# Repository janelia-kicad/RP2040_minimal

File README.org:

# This file is generated automatically from metadata
# File edits may be overwritten!
- Project Name: RP2040_minimal
- Synopsis: This minimal design example is intended to demonstrate how you can get started with your own RP2040 based PCB designs.
- Documentation Version: 1.0.0
- Pcb Version: 1.0
- Enclosure Version: 1.0
- Supplemental BOM Version: 1.0
- Release Date: 2024-04-24
- Creation Date: 2024-03-20
- Kicad Version: 7.0.11
- License: BSD-3-Clause
- URL: https://github.com/janelia-kicad/RP2040_minimal
- Author: Peter Polidoro
- Email: peter@polidoro.io
- Copyright: 2024 Howard Hughes Medical Institute
- References:
  - [[https://www.raspberrypi.com/products/raspberry-pi-pico/][Raspberry Pi Pico]]

[[./documentation/pcb/raytrace.png]]

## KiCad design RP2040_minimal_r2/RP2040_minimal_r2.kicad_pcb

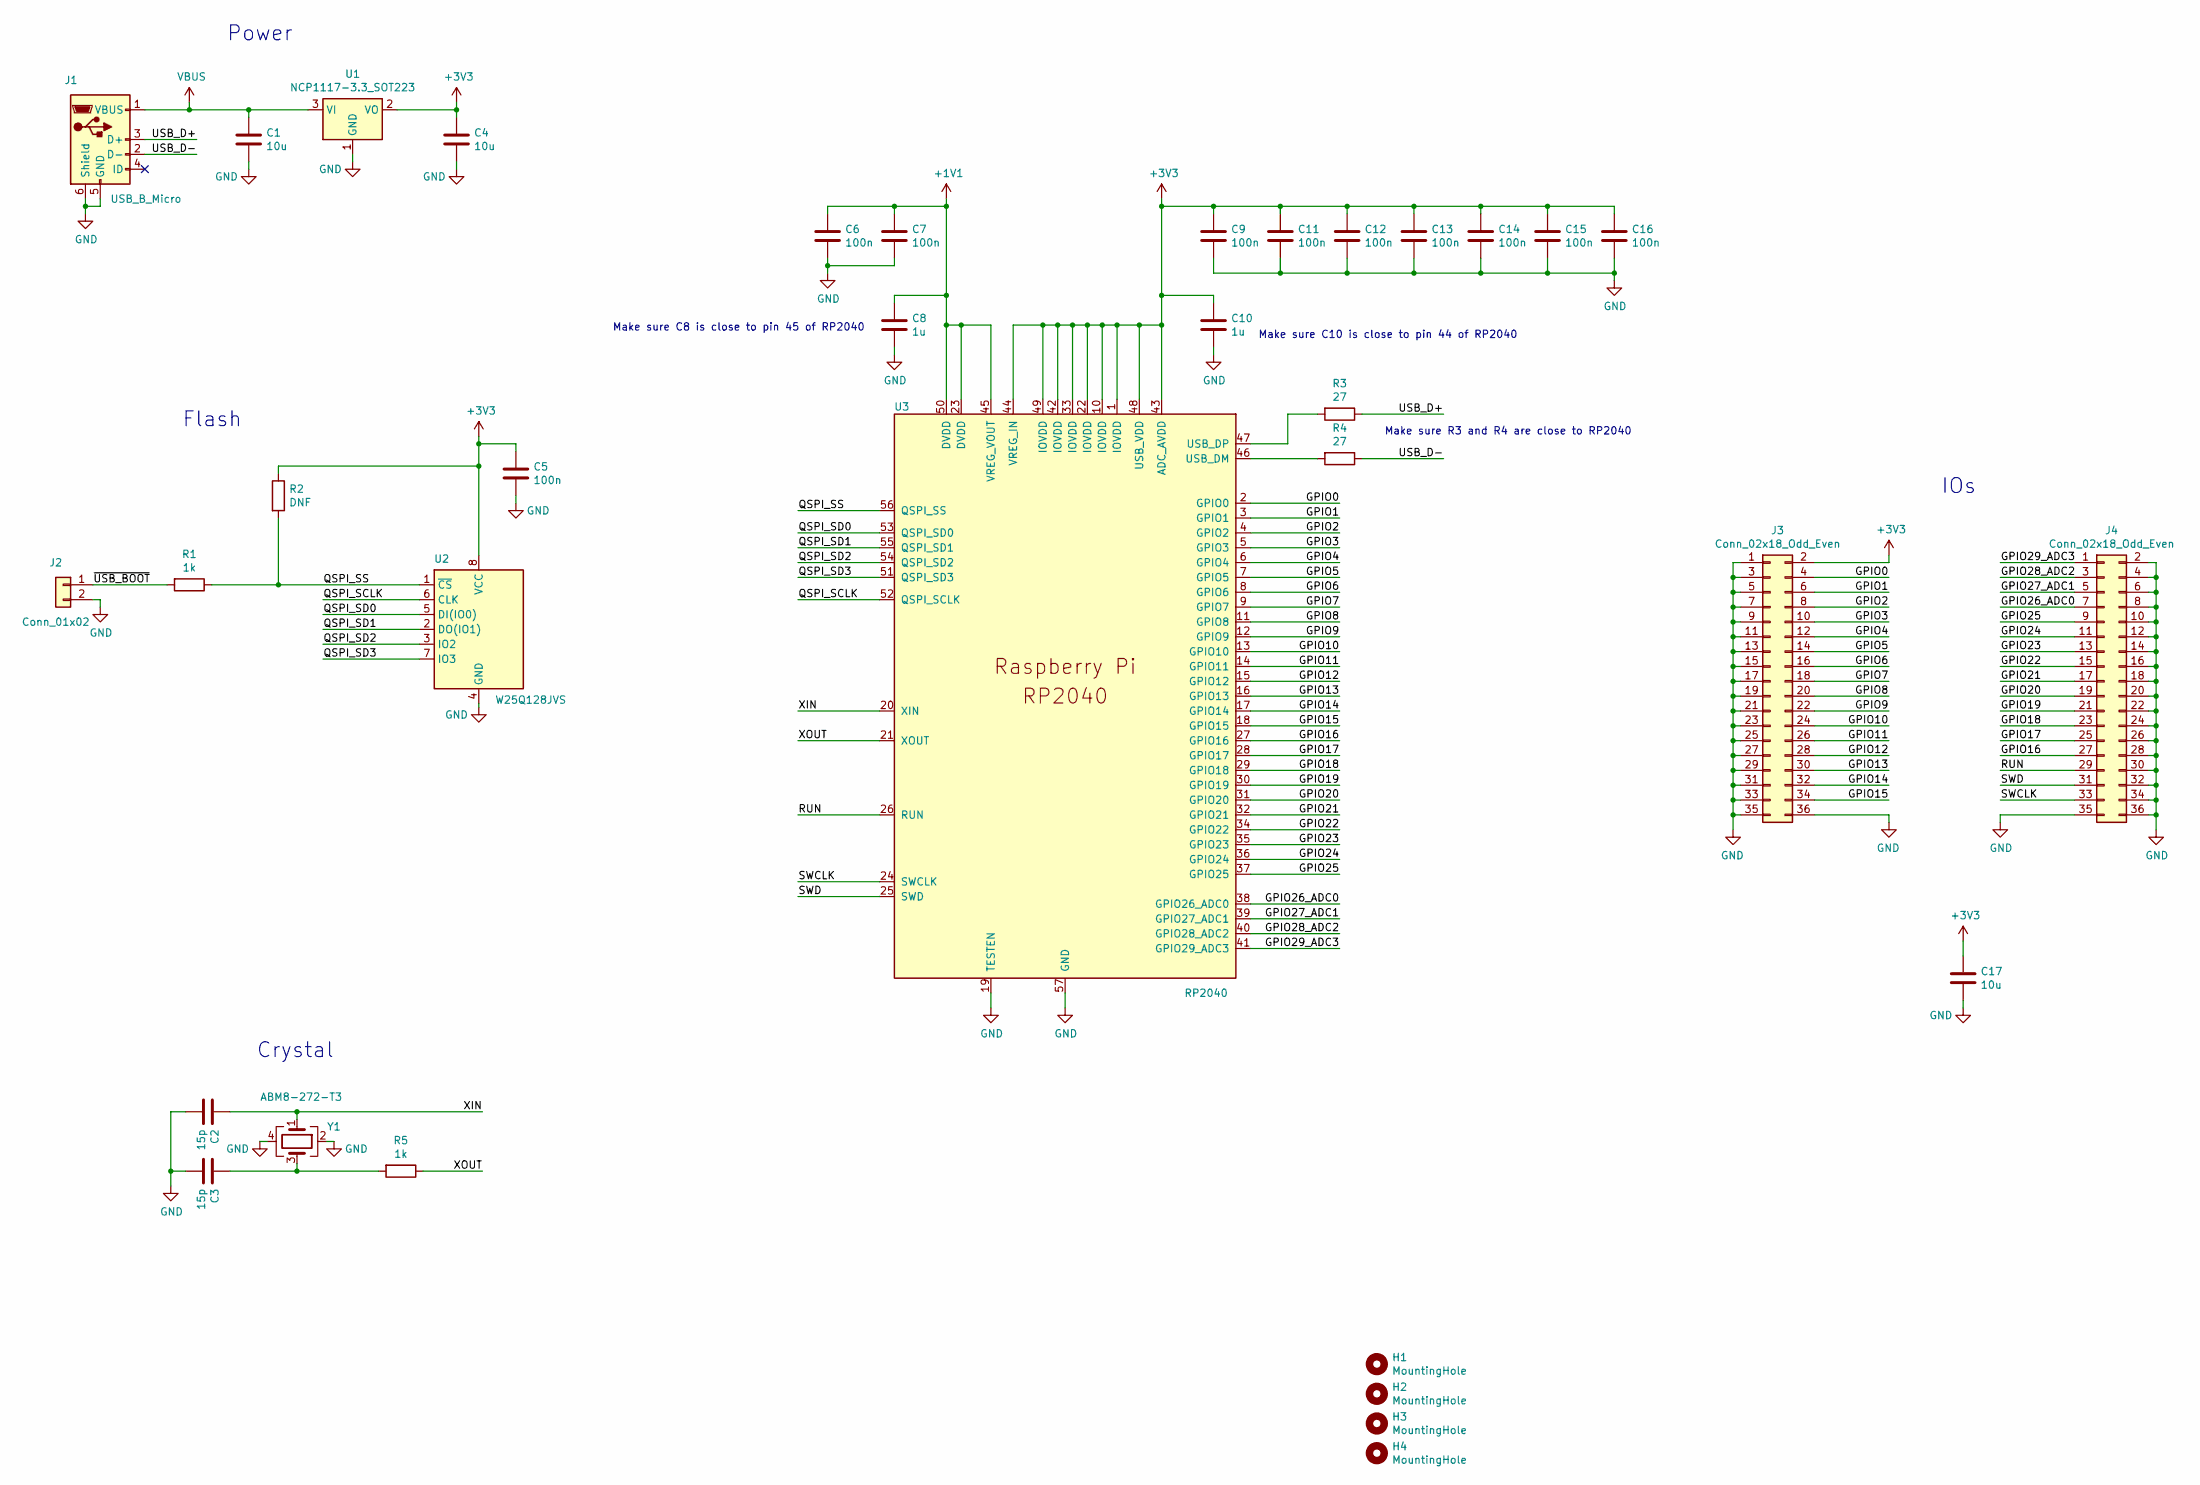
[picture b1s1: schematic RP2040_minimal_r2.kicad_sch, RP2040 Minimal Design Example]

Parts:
C1, C4, C17: 10u; C_0805_2012Metric
C2, C3: 15p; C_0402_1005Metric
C5, C6, C7, C9, C11, C12, C13, C14, C15, C16: 100n; C_0402_1005Metric
C8, C10: 1u; C_0402_1005Metric
H1, H2, H3, H4: MountingHole; MountingHole_2.7mm_M2.5
J1: USB_B_Micro; USB_Micro-B_Amphenol_10103594-0001LF_Horizontal_modified
J2: Conn_01x02; PinHeader_1x02_P2.54mm_Vertical
J3, J4: Conn_02x18_Odd_Even; PinHeader_2x18_P2.54mm_Vertical
R1, R5: 1k; R_0402_1005Metric
R2: DNF; R_0402_1005Metric
R3, R4: 27; R_0402_1005Metric
U1: NCP1117-3.3_SOT223; SOT-223-3_TabPin2
U2: W25Q128JVS; SOIC-8_5.23x5.23mm_P1.27mm
U3: RP2040; RP2040-QFN-56
Y1: ABM8-272-T3; Crystal_SMD_3225-4Pin_3.2x2.5mm

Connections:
+1V1: C6.1, C7.1, C8.1, U3.23 (DVDD), U3.45 (VREG_VOUT), U3.50 (DVDD)
+3V3: C4.1, C5.1, C9.1, C10.1, C11.1, C12.1, C13.1, C14.1, C15.1, C16.1, C17.1, J3.2, R2.1, U1.2 (VO), U2.8 (VCC), U3.1 (IOVDD), U3.10 (IOVDD), U3.22 (IOVDD), U3.33 (IOVDD), U3.42 (IOVDD), U3.43 (ADC_AVDD), U3.44 (VREG_IN), U3.48 (USB_VDD), U3.49 (IOVDD)
/GPIO0: J3.4, U3.2 (GPIO0)
/GPIO1: J3.6, U3.3 (GPIO1)
/GPIO2: J3.8, U3.4 (GPIO2)
/GPIO3: J3.10, U3.5 (GPIO3)
/GPIO4: J3.12, U3.6 (GPIO4)
/GPIO5: J3.14, U3.7 (GPIO5)
/GPIO6: J3.16, U3.8 (GPIO6)
/GPIO7: J3.18, U3.9 (GPIO7)
/GPIO8: J3.20, U3.11 (GPIO8)
/GPIO9: J3.22, U3.12 (GPIO9)
/GPIO10: J3.24, U3.13 (GPIO10)
/GPIO11: J3.26, U3.14 (GPIO11)
/GPIO12: J3.28, U3.15 (GPIO12)
/GPIO13: J3.30, U3.16 (GPIO13)
/GPIO14: J3.32, U3.17 (GPIO14)
/GPIO15: J3.34, U3.18 (GPIO15)
/GPIO16: J4.27, U3.27 (GPIO16)
/GPIO17: J4.25, U3.28 (GPIO17)
/GPIO18: J4.23, U3.29 (GPIO18)
/GPIO19: J4.21, U3.30 (GPIO19)
/GPIO20: J4.19, U3.31 (GPIO20)
/GPIO21: J4.17, U3.32 (GPIO21)
/GPIO22: J4.15, U3.34 (GPIO22)
/GPIO23: J4.13, U3.35 (GPIO23)
/GPIO24: J4.11, U3.36 (GPIO24)
/GPIO25: J4.9, U3.37 (GPIO25)
/GPIO26_ADC0: J4.7, U3.38 (GPIO26_ADC0)
/GPIO27_ADC1: J4.5, U3.39 (GPIO27_ADC1)
/GPIO28_ADC2: J4.3, U3.40 (GPIO28_ADC2)
/GPIO29_ADC3: J4.1, U3.41 (GPIO29_ADC3)
/QSPI_SCLK: U2.6 (CLK), U3.52 (QSPI_SCLK)
/QSPI_SD0: U2.5 (DI(IO0)), U3.53 (QSPI_SD0)
/QSPI_SD1: U2.2 (DO(IO1)), U3.55 (QSPI_SD1)
/QSPI_SD2: U2.3 (IO2), U3.54 (QSPI_SD2)
/QSPI_SD3: U2.7 (IO3), U3.51 (QSPI_SD3)
/QSPI_SS: R1.1, R2.2, U2.1 (~CS), U3.56 (QSPI_SS)
/RUN: J4.29, U3.26 (RUN)
/SWCLK: J4.33, U3.24 (SWCLK)
/SWD: J4.31, U3.25 (SWD)
/USB_D+: J1.3 (D+), R3.1
/USB_D-: J1.2 (D-), R4.1
/XIN: C2.1, U3.20 (XIN), Y1.1
/XOUT: R5.1, U3.21 (XOUT)
/~USB_BOOT: J2.1, R1.2
GND: C1.2, C2.2, C3.2, C4.2, C5.2, C6.2, C7.2, C8.2, C9.2, C10.2, C11.2, C12.2, C13.2, C14.2, C15.2, C16.2, C17.2, J1.5 (GND), J1.6 (Shield), J2.2, J3.1, J3.3, J3.5, J3.7, J3.9, J3.11, J3.13, J3.15, J3.17, J3.19, J3.21, J3.23, J3.25, J3.27, J3.29, J3.31, J3.33, J3.35, J3.36, J4.2, J4.4, J4.6, J4.8, J4.10, J4.12, J4.14, J4.16, J4.18, J4.20, J4.22, J4.24, J4.26, J4.28, J4.30, J4.32, J4.34, J4.35, J4.36, U1.1 (GND), U2.4 (GND), U3.19 (TESTEN), U3.57 (GND), Y1.2, Y1.4
unnamed: C3.1, R5.2, Y1.3
unnamed: R4.2, U3.46 (USB_DM)
unnamed: R3.2, U3.47 (USB_DP)
VBUS: C1.1, J1.1 (VBUS), U1.3 (VI)

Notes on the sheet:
IOs
Power
Crystal
Make sure C8 is close to pin 45 of RP2040
Make sure C10 is close to pin 44 of RP2040
Make sure R3 and R4 are close to RP2040
Flash

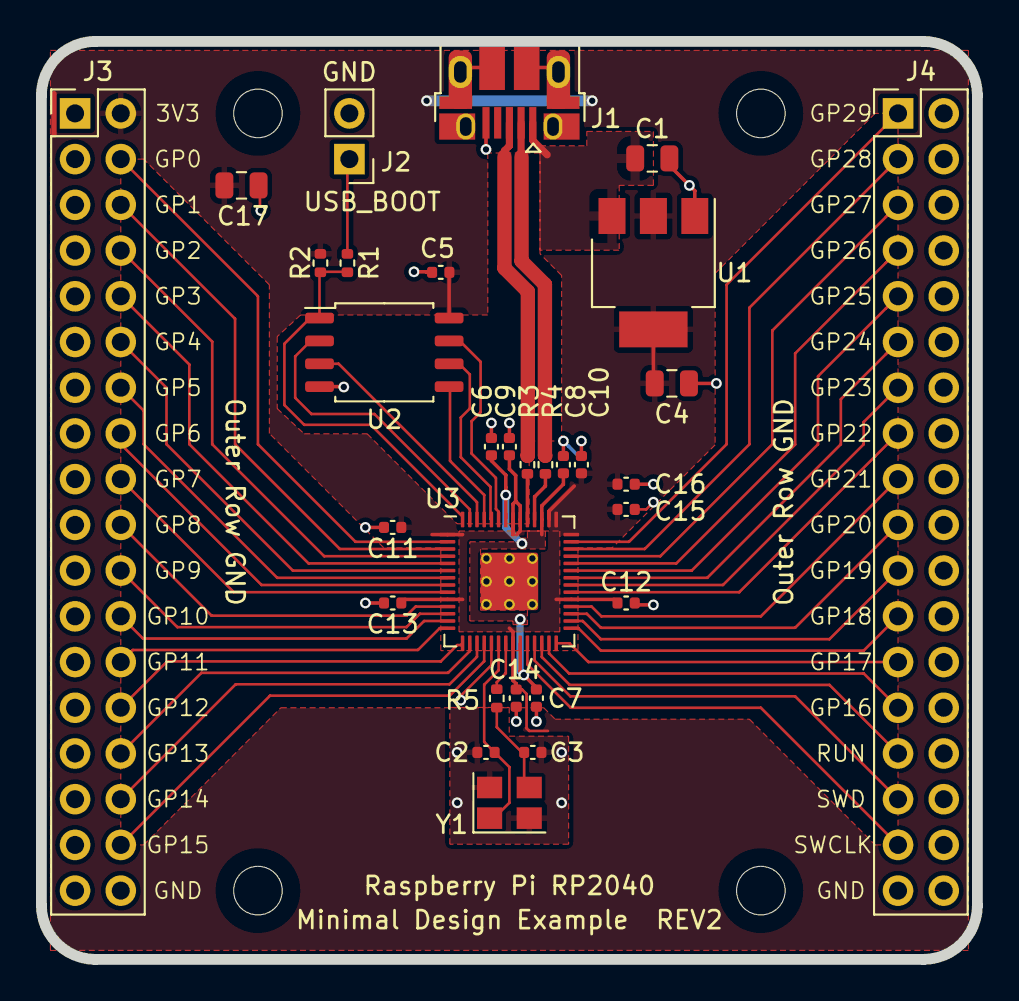
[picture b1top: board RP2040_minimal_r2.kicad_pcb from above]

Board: 2 copper layers, 52.0 x 51.0 mm, 34 parts (0 on the bottom side), 51 nets.

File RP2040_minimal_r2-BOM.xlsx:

RP2040_minimal_r2 BOM
Item | Quantity | Reference | Part | Voltage | Current | Power | Material | Size | Tolerance | Manufacturer | Manuf. Part # | Description | Notes
1 | 3 | C1,C4,C17 | 10u | 16V |  |  | X5R | 0805_2012Metric | 0.1 | Murata | GRM21BR61C106KE15K | CAP CER 10UF 16V X5R 0805 | Or equivalent
2 | 2 | C2, C3 | 15p | 50V |  |  | C0G | 0402_1005Metric | 0.05 | Murata | GCM1555C1H150JA16D | CAP CER 15PF 50V C0G/NP0 0402 | Or equivalent
3 | 10 | C5, C6, C7, C9, C11, C12, C13, C14, C15, C16 | 100n | 25V |  |  | X7R | 0402_1005Metric | 0.1 | Murata | GRM155R71E104KE14J | CAP CER 0.1UF 25V X7R 0402 | Or equivalent
4 | 2 | C8, C10 | 1u | 10V |  |  | X6S | 0402_1005Metric | 0.1 | Murata | GRM155C81A105KA12D | CAP CER 1UF 10V X6S 0402 | Or equivalent
5 | 1 | J1 | USB_B_Micro |  |  |  |  |  |  | Amphenol | 10103594-0001LF | CONN RCPT USB2.0 MICRO B SMD R/A | Or equivalent
6 | 1 | J2 | 1x2 way header |  |  |  |  |  |  | Samtec | TSW-102-23-T-S | 2.54mm pin header 1x2 | Or equivalent
7 | 2 | J3, J4 | 2x18 way header |  |  |  |  |  |  | Samtec | TSW-118-23-T-D | 2.54mm pin header 2x18 | Or equivalent
8 | 2 | R1, R5 | 1k |  |  | 63mW |  | 0402_1005Metric | 0.01 | Yageo | RC0402FR-071KP | RES SMD 1K OHM 1% 1/16W 0402 | Or equivalent
9 | 1 | R2 | DNF |  |  |  |  | 0402_1005Metric |  |  |  |  | Do Not Fit
10 | 2 | R3, R4 | 27.4 |  |  | 63mW |  | 0402_1005Metric | 0.01 | Yageo | RC0402FR-0727R4L | RES SMD 27.4 OHM 1% 1/16W 0402 | Or equivalent
11 | 1 | U1 | NCP1117-3.3 |  |  |  |  | SOT-223-3 |  | ON Semiconductor | NCP1117ST33T3G | IC REG LINEAR 3.3V 1A SOT223
12 | 1 | U2 | W25Q128JVS |  |  |  |  | SOIC-8 |  | Winbond | W25Q128JVSIQ TR | IC FLASH 128M SPI 133MHZ 8SOIC
13 | 1 | U3 | RP2040 |  |  |  |  | QFN56 |  | Raspberry Pi | RP2040
14 | 1 | Y1 | ABM8-272-T3 |  |  |  |  | SMD_3225 |  | Abracon | ABM8-272-T3 | CRYSTAL 12.0000MHZ 3.2x2.5MM SMD

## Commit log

2024-04-24 Add synopsis
2024-04-24 Opened files in KiCad
